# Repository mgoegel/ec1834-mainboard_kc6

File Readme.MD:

# robotron EC1834 Mainboard Schema

Der Robotron EC1834 ist ein 8086 basierter PC.

Hier ist die digitale Version des Schaltplans von 1988, inkl. Platinen-Layout.
Die Platine wurde aktuell noch nicht geroutet, da dies beträchtlicher Zeitaufwand ist.

Falls sich das jemand antun möchte, halte ich ihn nicht davon ab... ;-)

https://www.robotrontechnik.de/index.htm?/html/computer/ec1834.htm

## Anschlüsse

### Pin Header / Bus Connector

* X1.1-8 ISA Slots
* X2 Power 12P,12N,5N,GND
* X3 Power 5P, GND
* X4 Speaker
* X5 Power On LED
* X6 Reset
* X7 Keyboard

### Prüfstecker (PSx)

PS1 5x 8288 (In/Out) 
* 1=D4p19   S0 (Output)
* 2=D4p3    S1 (Output)
* 3=D4p18   S2 (Output)
* 4=D5p11   /ROMADRSEL (8xAND Input, Pull-Up)
* 5=frei

PS2 3x 8284 (Input) 
* 1=D43p1   CSYN (Input, Pull-Down)
* 2=D43p13  F/C (Input, Pull-Down)
* 3=D4314   EFI (Input, Offen)

PS3 9x 8253 (In/Out)
* 1=D60p10      /MEMW (FF Input vom Bus)
* 2=D88p4       /MEMW - WE (FF Output D60)
* 3=D72p1       /RAS1 (AND, Input, Pull-Up)
* 4=D72p4       /RAS0 (AND, Input, Pull-Up)
* 5=D72p9       /CASL (AND, Input, Pull-Up)
* 6=D72p13      /CASH (AND, Input, Pull-Up)
* 7=D48-D49p26  /INTA (PIC, Output)
* 8=frei
* 9=frei

PS4 3x D68  (Input)
* 1=D69p9       /MEMR (AND Input, Pull-Up)
* 2=D65p5       /DACK0BRD (Binary decoder A0-A2, Input E2, Pull-Down)
* 3=D85+86p15   ADRSEL (3s Q2 Data Selector, Input S, Pull-Down)

PS5 28x Edge-RAM (Output)
*  1=D109p2  MD1    Data
*  2=D108p2  MD2    Data
*  3=D110p2  MD0    Data
*  4=D79p2   MD10   Data
*  5=D107p2  MD3    Data
*  6=D104p2  MD6    Data
*  7=D78p2   MD11   Data
*  8=D106p2  MD4    Data
*  9=D103p2  MD7    Data
* 10=D113p5  MDPEE  Parity Even Input
* 11=D77p2   MD12   Data
* 12=D105p2  MD5    Data
* 13=D76p2   MD13   Data
* 14=D91p14  MDPOA  Parity Odd Output
* 15=D74p2   MD15   Data
* 16=D86p9   A5     Address
* 17=D86p12  A7     Address
* 18=D75p2   MD14   Data
* 19=D85p12  A0     Address
* 20=D85p9   A3     Address
* 21=D86p4   A4     Address
* 22=D86p7   A6     Address
* 23=D85p7   A1     Address
* 24=D85p4   A2     Address
* 25=D117p14 MDPEA  Parity Even Output
* 26=D114p5  MDPOE  Parity Odd Input
* 27=D80p2   MD9    Data
* 28=D81p2   MD8    Data

## R-Netzwerke

R9  4x 30R serie (8288)  
R10 9mx 4k7 bus (D27)  
R11 5x 1kR bus (verteilt)  
R12 9x 4k7 bus (verteilt)  
R14 4x 30R serie (D86) 
R15 4x 30R serie (D85) 
R16 4x 30R serie (D72)  
R23 9x 4k7 bus (DIP-EMR)  
R40 8x 4k7 bus (ROM D115)  
R41 8x 4k7 bus (ROM D100)  
R52 8x 3k9 bus (verteilt)

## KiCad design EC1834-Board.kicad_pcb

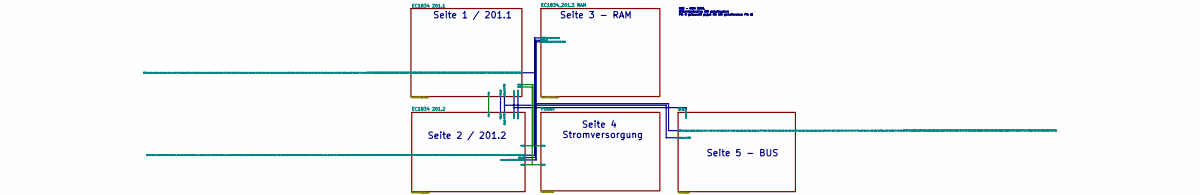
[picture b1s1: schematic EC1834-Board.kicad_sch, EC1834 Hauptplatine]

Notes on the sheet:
Seite 5 - BUS
R52 - KWH 3936, Widerstandsarray mit gemeinsamen Pin 8 getauscht gegen RN mit gemeinsamen Pin 1!
Seite 4 Stromversorgung
Seite 2 / 201.2
Seite 1 / 201.1
Seite 3 - RAM

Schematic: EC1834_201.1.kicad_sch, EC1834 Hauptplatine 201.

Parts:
Br4: Br4; R_Axial_DIN0204_L3.6mm_D1.6mm_P5.08mm_Horizontal
C5: 47µF; CP_Axial_L18.0mm_D6.5mm_P25.00mm_Horizontal
C6: 10nF; C_Disc_D4.3mm_W1.9mm_P5.00mm
C10: 10pF; C_Disc_D4.3mm_W1.9mm_P5.00mm
D1: K1810WM87; DIP-40_W15.24mm
D2, D25, D26, D45: DS8282; DIP-20_W7.62mm
D3, D11: DL020D; DIP-14_W7.62mm
D4: KR1810WG88; DIP-20_W7.62mm
D6, D28, D29: DL295; DIP-14_W7.62mm
D7, D37, D62: DL032D; DIP-14_W7.62mm
D8, D34, D59, D87: DL004D; DIP-14_W7.62mm
D9, D89: DS8205; DIP-16_W7.62mm
D10, D32, D39: 74S00; DIP-14_W7.62mm
D12, D40, D47, D88: DL008D; DIP-14_W7.62mm
D13, D15, D38, D51, D67, D126: DL074; DIP-14_W7.62mm
D14: DL010D; DIP-14_W7.62mm
D16: DL000; DIP-14_W7.62mm
D20: K1810WM86; DIP-40_W15.24mm
D21: DS8286D-D111; DIP-20_W7.62mm
D22, D83, D84: DS8286D; DIP-20_W7.62mm
D23, D64: DS8286D-D23; DIP-20_W7.62mm
D24: DL374; DIP-20_W7.62mm
D27: DS8286D-D27; DIP-20_W7.62mm
D33, D71: DL002D; DIP-14_W7.62mm
D35, D36: DL175; DIP-16_W7.62mm
D42: A302D; DIP-4_W7.62mm
D43: 8284; DIP-18_W7.62mm
D46, D61: DS8216; DIP-16_W7.62mm
D48, D49: KR580WN59A; DIP-28_W15.24mm
D50: KR580IK57; DIP-40_W15.24mm
D63: DL010D-D63; DIP-14_W7.62mm
E1, E2, E5: SolderJumper_2_Bridged; PinHeader_1x02_P2.54mm_Vertical
PS1: Conn_01x03; PinHeader_1x05_P2.54mm_Vertical
PS2: Conn_01x03; PinHeader_1x03_P2.54mm_Vertical
R1, R2: 4k7; R_Axial_L9.0mm_D1.8mm_P12.70mm_Horizontal
R3, R7, R8: 30; R_Axial_L9.0mm_D1.8mm_P12.70mm_Horizontal
R5, R6: 511; R_Axial_L9.0mm_D1.8mm_P12.70mm_Horizontal
R9: 30; R_Array_SIP8
R10, R12: 4k7; R_Array_SIP10
R11: 1k; R_Array_SIP6
R13: 4,7k; R_Axial_L9.0mm_D1.8mm_P12.70mm_Horizontal
R19: 18k; R_Axial_L9.0mm_D1.8mm_P12.70mm_Horizontal
R20: 180k; R_Axial_L9.0mm_D1.8mm_P12.70mm_Horizontal
R21: 100k; R_Axial_L9.0mm_D1.8mm_P12.70mm_Horizontal
R50, R51: 100; R_Axial_L9.0mm_D1.8mm_P12.70mm_Horizontal
R52: 3k9; R_Array_SIP8
V1: 14745,6KHz; Crystal_HC18-U_Horizontal
V2: SAY30; D_DO-35_SOD27_P2.54mm_Vertical_AnodeUp
W2, W3: Conn_01x01; PinHeader_1x01_P2.54mm_Vertical
WD1: WD1; R_Axial_DIN0204_L3.6mm_D1.6mm_P7.62mm_Horizontal
WD2: WD2; R_Axial_DIN0204_L3.6mm_D1.6mm_P7.62mm_Horizontal
WD3: WD3; R_Axial_DIN0204_L3.6mm_D1.6mm_P7.62mm_Horizontal
X6: RESET_BTN; PinHeader_1x02_P2.54mm_Vertical

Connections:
5PW1: D9.6 (E3), D64.11 (T), D83.11 (T), D84.11 (T); also elsewhere on the board
5PW2: D1.33 (~GT1), D20.31 (~GT0), D43.7 (AEN2), E1.1; also elsewhere on the board
+5V: D1.40 (VCC), D6.6 (V), D11.12 (C2), D13.4 (S), D15.1 (R), D15.4 (S), D15.10 (S), D15.13 (R), D20.40 (VCC), D28.6 (V), D29.6 (V), D38.1 (R), D42.1, D43.18 (VCC), D47.9 (A3), D51.10 (S), D126.1 (R), R1.1, R2.2, R10.1 (R1.1), R13.2, R19.2, R52.1 (R1.1); also elsewhere on the board
+12V: R20.2, V2.1 (K); also elsewhere on the board
/EC1834 201.1/1: D50.37 (A4), D64.5 (A4)
/EC1834 201.1/2: D50.38 (A5), D64.6 (A5)
/EC1834 201.1/3: D50.39 (A6), D64.7 (A6)
/EC1834 201.1/4: D50.40 (A7), D64.8 (A7)
/EC1834 201.1/A0: D2.18 (DO1), D40.13 (B4), D46.3 (DB0), D64.19 (B0); also elsewhere on the board
/EC1834 201.1/A1: D26.19 (DO0), D64.18 (B1), D83.2 (A1); also elsewhere on the board
/EC1834 201.1/A2: D26.18 (DO1), D64.17 (B2), D83.3 (A2); also elsewhere on the board
/EC1834 201.1/A3: D26.17 (DO2), D64.16 (B3), D83.4 (A3); also elsewhere on the board
/EC1834 201.1/A4: D26.16 (DO3), D64.15 (B4), D83.5 (A4); also elsewhere on the board
/EC1834 201.1/A5: D26.15 (DO4), D64.14 (B5), D83.6 (A5); also elsewhere on the board
/EC1834 201.1/A6: D26.14 (DO5), D64.13 (B6), D83.7 (A6); also elsewhere on the board
/EC1834 201.1/A7: D26.13 (DO6), D64.12 (B7), D83.8 (A7); also elsewhere on the board
/EC1834 201.1/A8: D25.19 (DO0), D45.19 (DO0), D84.1 (A0); also elsewhere on the board
/EC1834 201.1/A9: D25.18 (DO1), D45.18 (DO1), D84.2 (A1); also elsewhere on the board
/EC1834 201.1/A10: D25.17 (DO2), D45.17 (DO2), D84.3 (A2); also elsewhere on the board
/EC1834 201.1/A11: D25.16 (DO3), D45.16 (DO3), D84.4 (A3); also elsewhere on the board
/EC1834 201.1/A12: D25.15 (DO4), D45.15 (DO4), D84.5 (A4); also elsewhere on the board
/EC1834 201.1/A13: D25.14 (DO5), D45.14 (DO5), D83.1 (A0); also elsewhere on the board
/EC1834 201.1/A14: D25.13 (DO6), D45.13 (DO6); also elsewhere on the board
/EC1834 201.1/A15: D25.12 (DO7), D45.12 (DO7); also elsewhere on the board
/EC1834 201.1/A16: D2.15 (DO4), D6.13 (F0), D28.13 (F0), D29.13 (F0); also elsewhere on the board
/EC1834 201.1/A17: D2.14 (DO5), D6.12 (F1), D28.12 (F1), D29.12 (F1); also elsewhere on the board
/EC1834 201.1/A18: D2.13 (DO6), D6.11 (F2), D28.11 (F2), D29.11 (F2); also elsewhere on the board
/EC1834 201.1/A19: D2.16 (DO3), D6.10 (F3), D28.10 (F3), D29.10 (F3); also elsewhere on the board
/EC1834 201.1/AD0: D1.16 (AD0), D2.2 (DI1), D20.16 (AD0), D23.8 (A7), D24.12 (Q4), D26.8 (DI7)
/EC1834 201.1/AD1: D1.15 (AD1), D20.15 (AD1), D23.7 (A6), D24.9 (Q3), D26.1 (DI0)
/EC1834 201.1/AD2: D1.14 (AD2), D20.14 (AD2), D23.6 (A5), D24.6 (Q2), D26.2 (DI1)
/EC1834 201.1/AD3: D1.13 (AD3), D20.13 (AD3), D23.5 (A4), D24.15 (Q5), D26.3 (DI2)
/EC1834 201.1/AD4: D1.12 (AD4), D20.12 (AD4), D23.4 (A3), D24.16 (Q6), D26.4 (DI3)
/EC1834 201.1/AD5: D1.11 (AD5), D20.11 (AD5), D23.3 (A2), D24.5 (Q1), D26.5 (DI4)
/EC1834 201.1/AD6: D1.10 (AD6), D20.10 (AD6), D23.2 (A1), D24.2 (Q0), D26.6 (DI5)
/EC1834 201.1/AD7: D1.9 (AD7), D20.9 (AD7), D23.1 (A0), D24.19 (Q7), D26.7 (DI6)
/EC1834 201.1/AD8: D1.8 (AD8), D20.8 (AD8), D21.1 (A0), D25.1 (DI0)
/EC1834 201.1/AD9: D1.7 (AD9), D20.7 (AD9), D21.2 (A1), D25.2 (DI1)
/EC1834 201.1/AD10: D1.6 (AD10), D20.6 (AD10), D21.3 (A2), D25.3 (DI2)
/EC1834 201.1/AD11: D1.5 (AD11), D20.5 (AD11), D21.4 (A3), D25.4 (DI3)
/EC1834 201.1/AD12: D1.4 (AD12), D20.4 (AD12), D21.5 (A4), D25.5 (DI4)
/EC1834 201.1/AD13: D1.3 (AD13), D20.3 (AD13), D21.6 (A5), D25.6 (DI5)
/EC1834 201.1/AD14: D1.2 (AD14), D20.2 (AD14), D21.7 (A6), D25.7 (DI6)
/EC1834 201.1/AD15: D1.39 (AD15), D20.39 (AD15), D21.8 (A7), D25.8 (DI7)
/EC1834 201.1/AD16: D1.38 (A16), D2.5 (DI4), D20.38 (A16)
/EC1834 201.1/AD17: D1.37 (A17), D2.6 (DI5), D20.37 (A17)
/EC1834 201.1/AD18: D1.36 (A18), D2.7 (DI6), D20.36 (A18)
/EC1834 201.1/AD19: D1.35 (A19), D2.4 (DI3), D20.35 (A19)
/EC1834 201.1/AEN: D84.14 (B5); also elsewhere on the board
/EC1834 201.1/AENBRD: D12.13 (B4), D27.11 (T), D32.1 (A1), D35.2, D35.5 (D2), D39.1 (A1), D46.1 (CS), D83.9 (OE), WD1.2 (B); also elsewhere on the board
/EC1834 201.1/AENBRDW: D2.9 (OE), D4.6 (AEN), D25.9 (OE), D26.9 (OE), R10.10 (R9.2), WD1.1 (A)
/EC1834 201.1/AENDMA: D37.1 (A1), D39.2 (B1), D50.9 (AEN)
/EC1834 201.1/AENI: D12.11 (Y4), D32.12 (A4), D84.6 (A5)
/EC1834 201.1/ALE: D2.11 (STN), D25.11 (STN), D26.11 (STN), R8.1; also elsewhere on the board
/EC1834 201.1/BHE: D47.12 (A4); also elsewhere on the board
/EC1834 201.1/BS-/WAIT: D14.2 (B1), D38.5
/EC1834 201.1/CAS0: D48.12 (CAS0), D49.12 (CAS0)
/EC1834 201.1/CAS1: D48.13 (CAS1), D49.13 (CAS1)
/EC1834 201.1/CAS2: D48.15 (CAS2), D49.15 (CAS2)
/EC1834 201.1/CEN: D4.15 (CEN), D12.6 (Y2)
/EC1834 201.1/CLK: D35.9 (C), D38.11 (C), D84.13 (B6); also elsewhere on the board
/EC1834 201.1/CLK86: D1.19 (CLK), D4.2 (CLK), D20.19 (CLK), D84.7 (A6), D87.13 (A6), D126.3 (C), R3.1; also elsewhere on the board
/EC1834 201.1/D0: D22.19 (B0), D23.12 (B7), D24.13 (D4); also elsewhere on the board
/EC1834 201.1/D1: D22.18 (B1), D23.13 (B6), D24.8 (D3); also elsewhere on the board
/EC1834 201.1/D2: D22.17 (B2), D23.14 (B5), D24.7 (D2); also elsewhere on the board
/EC1834 201.1/D3: D22.16 (B3), D23.15 (B4), D24.14 (D5); also elsewhere on the board
/EC1834 201.1/D4: D22.15 (B4), D23.16 (B3), D24.17 (D6); also elsewhere on the board
/EC1834 201.1/D5: D22.14 (B5), D23.17 (B2), D24.4 (D1); also elsewhere on the board
/EC1834 201.1/D6: D22.13 (B6), D23.18 (B1), D24.3 (D0); also elsewhere on the board
/EC1834 201.1/D7: D22.12 (B7), D23.19 (B0), D24.18 (D7); also elsewhere on the board
/EC1834 201.1/D8: D21.19 (B0), D22.1 (A0); also elsewhere on the board
/EC1834 201.1/D9: D21.18 (B1), D22.2 (A1); also elsewhere on the board
/EC1834 201.1/D10: D21.17 (B2), D22.3 (A2); also elsewhere on the board
/EC1834 201.1/D11: D21.16 (B3), D22.4 (A3); also elsewhere on the board
/EC1834 201.1/D12: D21.15 (B4), D22.5 (A4); also elsewhere on the board
/EC1834 201.1/D13: D21.14 (B5), D22.6 (A5); also elsewhere on the board
/EC1834 201.1/D14: D21.13 (B6), D22.7 (A6); also elsewhere on the board
/EC1834 201.1/D15: D21.12 (B7), D22.8 (A7); also elsewhere on the board
/EC1834 201.1/DACK0: D8.12 (Y6), D51.12 (D); also elsewhere on the board
/EC1834 201.1/DEN: D4.16 (DEN), D8.3 (A2), D11.13 (D2)
/EC1834 201.1/DRQ0: D50.19 (DRQ0); also elsewhere on the board
/EC1834 201.1/DRQ1: D50.18 (DRQ1); also elsewhere on the board
/EC1834 201.1/DRQ2: D50.17 (DRQ2); also elsewhere on the board
/EC1834 201.1/DRQ3: D50.16 (DRQ3); also elsewhere on the board
/EC1834 201.1/DT-/R: D4.4 (DT/~R), D16.4 (A2), D21.11 (T), D23.11 (T)
/EC1834 201.1/HOLDA: D50.7 (HLDA), D51.5
/EC1834 201.1/HRQDMA: D38.13 (R), D50.10 (HRQ), D51.1 (R)
/EC1834 201.1/IED: D38.8, D38.10 (S), D40.10 (B3)
/EC1834 201.1/INT: D20.18 (INTR), D49.17 (INT)
/EC1834 201.1/IOCHRDY: D14.1 (A1), D67.10 (S), R13.1; also elsewhere on the board
/EC1834 201.1/IORW: D7.2 (B1), D10.3 (Y1), D67.11 (C)
/EC1834 201.1/IRQ0: D49.18 (IR0); also elsewhere on the board
/EC1834 201.1/IRQ1: D49.19 (IR1); also elsewhere on the board
/EC1834 201.1/IRQ2: Br4.1 (A), Br4.2 (B), D48.17 (INT), D48.19 (IR1), D49.20 (IR2); also elsewhere on the board
/EC1834 201.1/IRQ3: D49.21 (IR3); also elsewhere on the board
/EC1834 201.1/IRQ4: D49.22 (IR4); also elsewhere on the board
/EC1834 201.1/IRQ5: D49.23 (IR5); also elsewhere on the board
/EC1834 201.1/IRQ6: D49.24 (IR6); also elsewhere on the board
/EC1834 201.1/IRQ7: D49.25 (IR7); also elsewhere on the board
/EC1834 201.1/IRQ8: D48.18 (IR0), D51.9
/EC1834 201.1/IRQ10: D48.20 (IR2); also elsewhere on the board
/EC1834 201.1/IRQ11: D48.21 (IR3); also elsewhere on the board
/EC1834 201.1/IRQ12: D48.22 (IR4); also elsewhere on the board
/EC1834 201.1/IRQ14: D48.24 (IR6); also elsewhere on the board
/EC1834 201.1/IRQ15: D48.25 (IR7); also elsewhere on the board
/EC1834 201.1/MASTER: D8.2 (Y1), D27.9 (OE), D33.6 (B2), D33.9 (B3), D33.12 (B4), D62.2 (B1)
/EC1834 201.1/MEMR: D11.10 (B2); also elsewhere on the board
/EC1834 201.1/NMI: D20.17 (NMI); also elsewhere on the board
/EC1834 201.1/NPNPI: D1.32 (INT), D48.23 (IR5); also elsewhere on the board
/EC1834 201.1/OSC1: E5.2; also elsewhere on the board
/EC1834 201.1/PB3: D51.13 (R); also elsewhere on the board
/EC1834 201.1/PCLK: D50.12 (CLK), D51.3 (C), R7.1; also elsewhere on the board
/EC1834 201.1/PS1:4: PS1.4; also elsewhere on the board
/EC1834 201.1/QS0: D1.25 (QS0), D20.25 (QS0)
/EC1834 201.1/QS1: D1.24 (QS1), D20.24 (QS1)
/EC1834 201.1/RDY-/WAIT: D14.13 (C1), D47.1 (A1), D67.8
/EC1834 201.1/RDYTODMA: D47.3 (Y1), D50.6 (RDY)
/EC1834 201.1/READY: D1.22 (READY), D20.22 (READY), D43.5 (READY)
/EC1834 201.1/RESET: D1.21 (RESET), D20.21 (RESET), D34.11 (A5), D43.10 (RESET), D50.13 (RESET); also elsewhere on the board
/EC1834 201.1/RESETDRV: D59.2 (Y1)
/EC1834 201.1/TC: D47.8 (Y3), D51.11 (C); also elsewhere on the board
/EC1834 201.1/VA0: D26.12 (DO7), D33.3 (B1), D88.12 (A4)
/EC1834 201.1/WRTDMAPGREG: D9.3 (A2), D71.10 (Y3)
/EC1834 201.1/XA0: D9.1 (A0), D48.27 (A0), D49.27 (A0), D50.32 (A0), D64.1 (A0); also elsewhere on the board
/EC1834 201.1/XA1: D9.2 (A1), D50.33 (A1), D64.2 (A1), D83.18 (B1); also elsewhere on the board
/EC1834 201.1/XA2: D50.34 (A2), D64.3 (A2), D83.17 (B2); also elsewhere on the board
/EC1834 201.1/XA3: D50.35 (A3), D64.4 (A3), D83.16 (B3); also elsewhere on the board
/EC1834 201.1/XA4: D83.15 (B4); also elsewhere on the board
/EC1834 201.1/XA5: D83.14 (B5), D89.1 (A0); also elsewhere on the board
/EC1834 201.1/XA6: D83.13 (B6), D89.2 (A1); also elsewhere on the board
/EC1834 201.1/XA7: D83.12 (B7), D89.3 (A2); also elsewhere on the board
/EC1834 201.1/XA8: D84.19 (B0), D89.4 (E1); also elsewhere on the board
/EC1834 201.1/XA9: D84.18 (B1), D89.5 (E2); also elsewhere on the board
/EC1834 201.1/XA10: D84.17 (B2); also elsewhere on the board
/EC1834 201.1/XA11: D84.16 (B3); also elsewhere on the board
/EC1834 201.1/XA12: D84.15 (B4); also elsewhere on the board
/EC1834 201.1/XA13: D83.19 (B0); also elsewhere on the board
/EC1834 201.1/XD0: D6.2 (A1), D28.2 (A1), D29.2 (A1), D45.1 (DI0), D48.11 (D0), D49.11 (D0), D50.30 (DB0); also elsewhere on the board
/EC1834 201.1/XD1: D6.3 (A2), D28.3 (A2), D29.3 (A2), D45.2 (DI1), D48.10 (D1), D49.10 (D1), D50.29 (DB1); also elsewhere on the board
/EC1834 201.1/XD2: D6.4 (A3), D28.4 (A3), D29.4 (A3), D45.3 (DI2), D48.9 (D2), D49.9 (D2), D50.28 (DB2); also elsewhere on the board
/EC1834 201.1/XD3: D6.5 (A4), D28.5 (A4), D29.5 (A4), D45.4 (DI3), D48.8 (D3), D49.8 (D3), D50.27 (DB3); also elsewhere on the board
/EC1834 201.1/XD4: D45.5 (DI4), D48.7 (D4), D49.7 (D4), D50.26 (DB4); also elsewhere on the board
/EC1834 201.1/XD5: D45.6 (DI5), D48.6 (D5), D49.6 (D5), D50.23 (DB5); also elsewhere on the board
/EC1834 201.1/XD6: D45.7 (DI6), D48.5 (D6), D49.5 (D6), D50.22 (DB6); also elsewhere on the board
/EC1834 201.1/XD7: D45.8 (DI7), D48.4 (D7), D49.4 (D7), D50.21 (DB7); also elsewhere on the board
/EC1834 201.1/~A0: D61.12 (DI3); also elsewhere on the board
/EC1834 201.1/~AEN: D12.5 (B2), D16.5 (B2), D35.3, D67.12 (D), D89.6 (E3); also elsewhere on the board
/EC1834 201.1/~BHE: D1.34 (BHE), D2.8 (DI7), D2.12 (DO7), D7.5 (B2), D20.34 (BHE), D33.2 (A1), D61.13 (DB3); also elsewhere on the board
/EC1834 201.1/~CIOR: D4.13 (IORC), D27.14 (B5), R9.6 (R3.2), R10.7 (R6.2)
/EC1834 201.1/~CIOW: D4.12 (AIOWC), D27.12 (B7), R9.8 (R4.2), R10.9 (R8.2)
/EC1834 201.1/~CLK: D13.1 (R), D15.3 (C), D15.11 (C), D36.9 (C), D87.12 (Y6)
/EC1834 201.1/~CMEMR: D4.7 (MRDC), D27.18 (B1), R9.2 (R1.2), R10.3 (R2.2)
/EC1834 201.1/~CMEMW: D4.8 (AMWC), D27.16 (B3), R9.4 (R2.2), R10.5 (R4.2)
/EC1834 201.1/~CS86H: D7.6 (Y2), D21.9 (OE)
/EC1834 201.1/~CS86L: D7.8 (Y3), D23.9 (OE)
/EC1834 201.1/~DACK0BRD: D8.13 (A6), D50.25 (DACK0), D84.8 (A7); also elsewhere on the board
/EC1834 201.1/~DACK0: D40.2 (B1), D84.12 (B7); also elsewhere on the board
/EC1834 201.1/~DACK1: D40.1 (A1), D50.24 (DACK1); also elsewhere on the board
/EC1834 201.1/~DACK2: D33.8 (A3), D50.14 (DACK2); also elsewhere on the board
/EC1834 201.1/~DACK3: D33.11 (A4), D50.15 (DACK3); also elsewhere on the board
/EC1834 201.1/~DMAAEN: D39.3 (Y1), D62.1 (A1)
/EC1834 201.1/~DMACS: D50.11 (CS), D89.15 (O0)
/EC1834 201.1/~DMAWAIT: D40.8 (Y3), D126.4 (S)
/EC1834 201.1/~F2: D35.6, D40.9 (A3)
/EC1834 201.1/~F4: D35.14, D39.10 (B3)
/EC1834 201.1/~GT1: D1.31 (~GT0), D20.30 (~GT1), R1.2
/EC1834 201.1/~INTA: D4.14 (~INTA), D48.26 (INTA), D49.26 (INTA), D88.13 (B4), R52.2 (R1.2); also elsewhere on the board
/EC1834 201.1/~INTRCS1: D49.1 (CS), D89.14 (O1)
/EC1834 201.1/~INTRCS2: D48.1 (CS), D89.9 (O6)
/EC1834 201.1/~IOR: R9.5 (R3.1); also elsewhere on the board
/EC1834 201.1/~IOW: R9.7 (R4.1); also elsewhere on the board
/EC1834 201.1/~LOCK: D3.13 (D2), D20.29 (~LOCK)
/EC1834 201.1/~MASTER: D8.1 (A1), D12.12 (A4), D47.13 (B4), R11.4 (R3.2); also elsewhere on the board
/EC1834 201.1/~MEMADRSEL: D88.10 (B3); also elsewhere on the board
/EC1834 201.1/~MEMCS16: D88.9 (A3), R11.5 (R4.2); also elsewhere on the board
/EC1834 201.1/~MEMR: D32.4 (A2), R9.1 (R1.1); also elsewhere on the board
/EC1834 201.1/~MEMW: D32.5 (B2), R9.3 (R2.1); also elsewhere on the board
/EC1834 201.1/~NMIADRCS: D71.8 (A3), D89.11 (O4); also elsewhere on the board
/EC1834 201.1/~NMIREGCS: D89.10 (O5); also elsewhere on the board
/EC1834 201.1/~PPICS: D89.12 (O3); also elsewhere on the board
/EC1834 201.1/~RESETDRV: D12.2 (B1), D12.10 (B3), D34.10 (Y5), D35.1 (R), D59.1 (A1), R12.3 (R2.2); also elsewhere on the board
/EC1834 201.1/~S0: D1.26 (S0), D3.9 (A2), D4.19 (S0), D20.26 (S0), PS1.1
/EC1834 201.1/~S1: D1.27 (S1), D3.10 (B2), D4.3 (S1), D20.27 (S1), PS1.2
/EC1834 201.1/~S2: D1.28 (S2), D3.12 (C2), D4.18 (S2), D20.28 (S2), PS1.3
/EC1834 201.1/~TIMERCS: D89.13 (O2); also elsewhere on the board
/EC1834 201.1/~XIOR: D10.1 (A1), D27.6 (A5), D27.15 (B4), D48.3 (RD), D49.3 (RD), R10.6 (R5.2); also elsewhere on the board
/EC1834 201.1/~XIOW: D10.2 (B1), D27.8 (A7), D27.13 (B6), D48.2 (WR), D49.2 (WR), D71.9 (B3), R10.8 (R7.2); also elsewhere on the board
/EC1834 201.1/~XMEMR: D27.2 (A1), D50.3 (MEMR), R10.2 (R1.2); also elsewhere on the board
/EC1834 201.1/~XMEMW: D27.4 (A3), D32.13 (B4), D50.4 (MEMW), R10.4 (R3.2)
/EC1834 201.1/~YIOR: D27.5 (A4), D50.1 (IOR), R12.6 (R5.2), R12.9 (R8.2)
/EC1834 201.1/~YIOW: D27.7 (A6), D50.2 (IOW)
GND: C5.1, C6.1, D1.1 (GND), D1.20 (GND), D4.1 (IOB), D6.1 (A0), D9.4 (E1), D9.5 (E2), D20.1 (GND), D20.20 (GND), D20.33 (MAX), D28.1 (A0), D29.1 (A0), D38.2 (D), D42.3, D43.6 (RDY2), D46.7 (DI1), D46.9 (DI2), D46.12 (DI3), D46.15 (DIEN), D48.16 (SP), D61.4 (DI0), D61.7 (DI1), D61.9 (DI2), D61.15 (DIEN), D84.9 (OE), R5.1, R6.2, R21.1, R50.1, R51.1, X6.1; also elsewhere on the board
unnamed: C5.2, D42.2, R20.1, R21.2, V2.2 (A)
unnamed: C6.2, D42.4, D43.11 (RES), R19.1, X6.2
unnamed: C10.1, D43.17 (X1), R6.1
unnamed: C10.2, V1.2
unnamed: D1.23 (BUSY), D20.23 (TEST), R2.1
unnamed: D3.8 (Y2), D34.1 (A1)
unnamed: D4.5 (ALE), R8.2
unnamed: D6.9 (C), D8.6 (Y3)
unnamed: D7.4 (A2), D7.9 (A3), D8.4 (Y2)
unnamed: D7.12 (A4), D88.11 (Y4)
unnamed: D8.5 (A3), D9.7 (O7)
unnamed: D8.9 (A4), D9.10 (O5)
unnamed: D8.11 (A5), D9.9 (O6)
unnamed: D11.8 (Y2), WD2.2 (B)
unnamed: D11.9 (A2), D36.10, D36.13 (D4)
unnamed: D12.1 (A1), D13.6
unnamed: D12.3 (Y1), D36.1 (R)
unnamed: D12.4 (A2), D32.8 (Y3)
unnamed: D12.8 (Y3), D38.4 (S)
unnamed: D12.9 (A3), D36.14
unnamed: D13.2 (D), D36.15
unnamed: D13.3 (C), D59.10 (Y5)
unnamed: D14.8 (Y3), D34.3 (A2)
unnamed: D14.9 (A3), D33.1 (Y1)
unnamed: D14.10 (B3), D32.6 (Y2), D40.4 (A2), D59.11 (A5)
unnamed: D14.11 (C3), D32.2 (B1), D40.5 (B2), D88.8 (Y3)
unnamed: D15.2 (D), D38.6
unnamed: D15.5, D36.4 (D1)
unnamed: D7.13 (B4), D15.9
unnamed: D15.12 (D), D24.11 (C), D32.9 (A3), D36.7, D36.12 (D3)
unnamed: D16.1 (A1), D32.11 (Y4)
unnamed: D16.2 (B1), D16.6 (Y2)
unnamed: D16.3 (Y1), D22.11 (T)
unnamed: D22.9 (OE), R12.7 (R6.2), WD3.2 (B)
unnamed: D24.1 (OE), R12.8 (R7.2), WD2.1 (A)
unnamed: D28.8 (CS), D33.10 (Y3)
unnamed: D8.8 (Y4), D28.9 (C)
unnamed: D29.8 (CS), D33.13 (Y4)
unnamed: D8.10 (Y5), D29.9 (C)
unnamed: D32.3 (Y1), D40.12 (A4)
unnamed: D32.10 (B3), D36.11
unnamed: D6.8 (CS), D33.4 (Y2)
unnamed: D33.5 (A2), D40.3 (Y1)
unnamed: D34.2 (Y1), D38.12 (D)
unnamed: D34.4 (Y2), D38.3 (C)
unnamed: D35.4 (D1), D37.3 (Y1)
unnamed: D35.10, D35.13 (D4)
unnamed: D35.11, D47.2 (B1), D67.13 (R)
unnamed: D35.12 (D3), D67.9
unnamed: D36.2, D39.9 (A3)
unnamed: D36.5 (D2), D39.11 (Y4)
unnamed: D36.6, D39.12 (A4)
unnamed: D37.2 (B1), D38.9, D51.2 (D)
unnamed: D39.8 (Y3), D39.13 (B4)
unnamed: D7.1 (A1), D40.6 (Y2)
unnamed: D40.11 (Y4), D63.3 (A2)
unnamed: D43.1 (CSYN), PS2.1, R51.2
unnamed: D43.2 (PC), R7.2
unnamed: D43.8 (CLK), R3.2
unnamed: D43.12 (OSC), E5.1
unnamed: D43.13 (F/C), E2.2
unnamed: D43.14 (EFI), PS2.3, W2.1
unnamed: D43.15 (ASYN), E1.2
unnamed: D43.16 (X2), R5.2, V1.1
unnamed: D45.9 (OE), D61.1 (CS), D62.3 (Y1), D64.9 (OE)
unnamed: D45.11 (STN), D50.8 (ADSTB)
unnamed: D7.10 (B3), D7.11 (Y4), D46.4 (DI0)
unnamed: D47.10 (B3), D50.36 (TC)
unnamed: D47.11 (Y4), D63.5 (C2)
unnamed: D49.16 (SP), R12.10 (R9.2)
unnamed: D51.4 (S), D51.6
unnamed: D7.3 (Y1), D63.4 (B2)
unnamed: D63.6 (Y2), WD3.1 (A)
unnamed: D89.7 (O7), W3.1
unnamed: D14.12 (Y1), D43.3 (AEN1), D126.2 (D)
unnamed: D43.4 (RDY1), D126.6
unnamed: E2.1, PS2.2, R50.2

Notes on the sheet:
Bei der Verwend. d. K1810GF84 entfällt E1
offen!
D5 p11 Koord C1 / Blatt 201.2
H, wenn kein Speicherzugriff
H PullUp R10
Durch WD3 deaktiviert
X1 Bus Connector auf Seite "BUS"
L, wenn kein Speicherzugriff
WDx - Drahtbrücken
D64A PIN Pos abweichend von Zeichnung 1.13.120030.0/04
L in CPU Zyklus T3 oder RDY LOW
DMA Page Register Steuerung
Durch WD2 deaktiviert
